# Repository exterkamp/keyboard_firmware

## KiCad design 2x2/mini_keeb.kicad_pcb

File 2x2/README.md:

# Code 2x2 Mini Keyboard

## What's in the box

* [Electronic Schematics.](mini_keeb.sch) 
* [Kicad PCB layouts.](mini_keeb.kicad_pcb) 
* [Firmware to drive the keyboard.](2x2_firmware.ino)

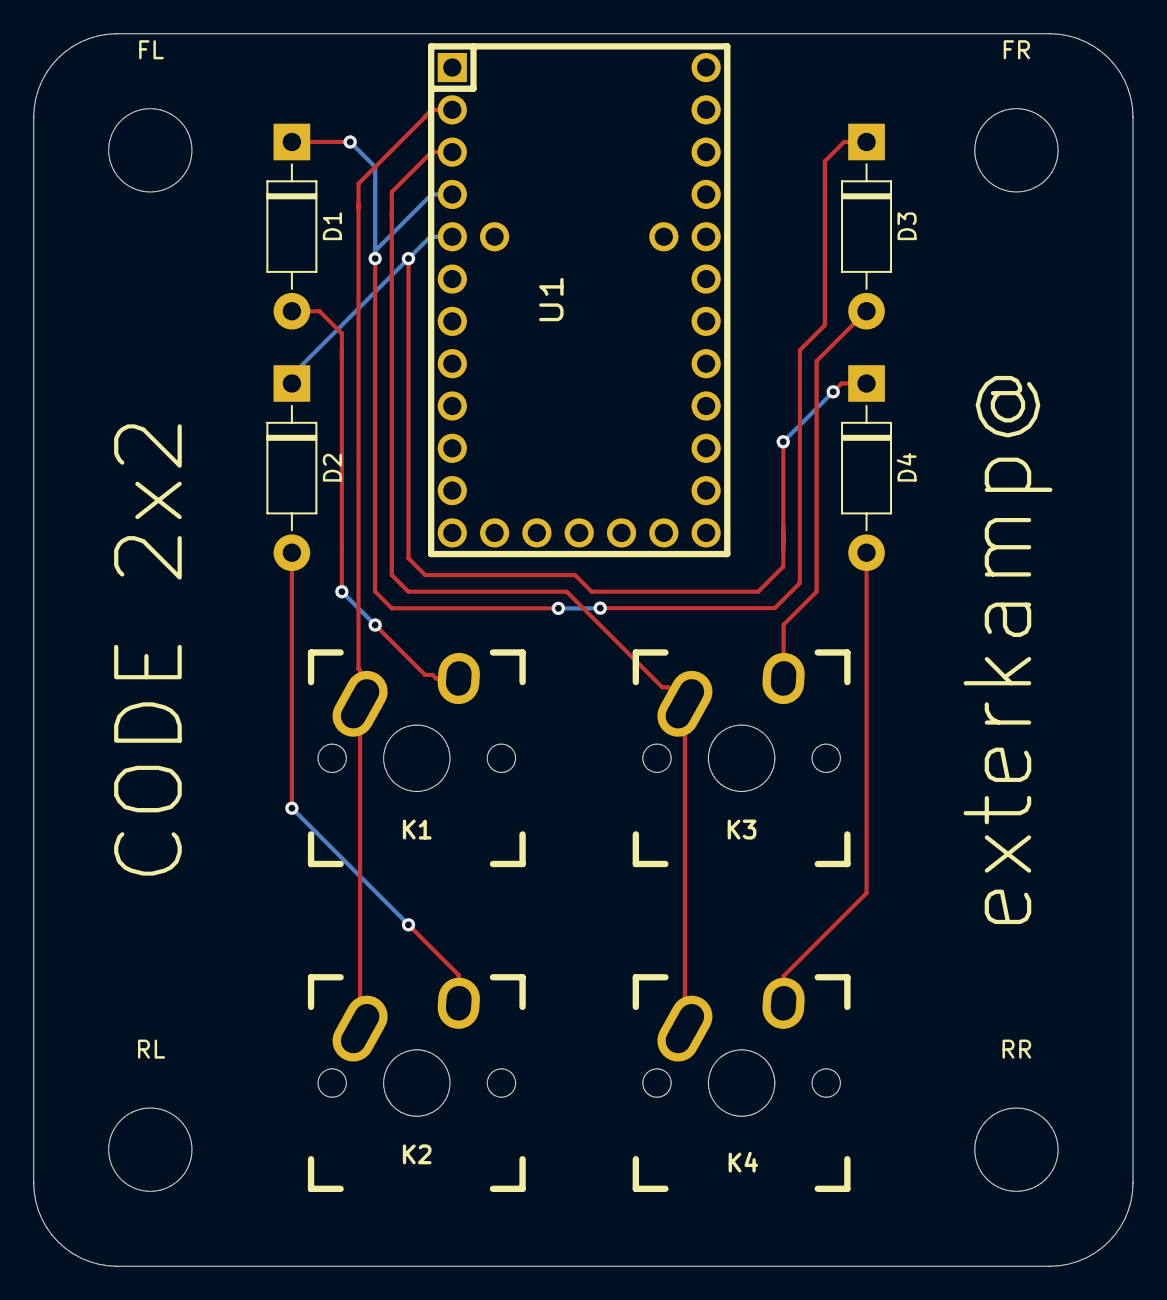
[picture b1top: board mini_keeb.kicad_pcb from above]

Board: 2 copper layers, 66.0 x 74.0 mm, 13 parts (0 on the bottom side), 10 nets.

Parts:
D1, D2, D3, D4: D; D_DO-41_SOD81_P10.16mm_Horizontal
FL: MountingHole_5mm
FR: MountingHole_5mm
K1, K2, K3, K4: KEYSW; Mx_Alps_100
RL: MountingHole_5mm
RR: MountingHole_5mm
U1: Teensy2.0; Teensy_20

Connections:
/col0: K1.1, K2.1, U1.2
/col1: K3.1, K4.1, U1.3
/row0: D1.1, D3.1, U1.4
/row1: D2.1, D4.1, U1.5
GND: U1.1, U1.15
unnamed: D1.2, K1.2
unnamed: D2.2, K2.2
unnamed: D3.2, K3.2
unnamed: D4.2, K4.2
VCC: U1.14, U1.29

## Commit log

2019-05-24 Init w/readme
2019-05-24 Add 2x2 firmware, schematics, and pcb.
2019-05-24 Add 2x2 README
2019-05-24 Update to comment
2020-03-29 New firmware for larger 69 key board
